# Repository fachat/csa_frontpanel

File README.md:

# CS/A frontpanel design

This repo defines a front panel with toggle switches and push buttons to
read data from and write data to CS/A memory bus.

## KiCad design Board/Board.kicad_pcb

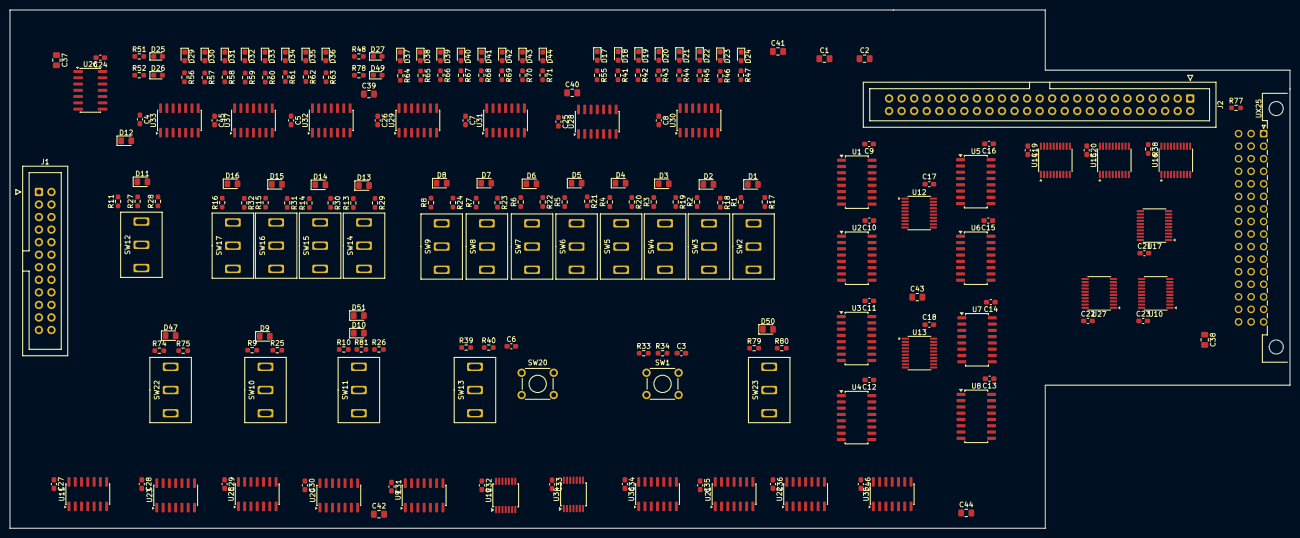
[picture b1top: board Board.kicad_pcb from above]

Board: 2 copper layers, 259.1 x 104.9 mm, 221 parts (0 on the bottom side), 267 nets, no tracks yet.

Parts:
C1, C2, C37, C38, C39, C40, C41, C42, C43, C44: 47u; C_0805_2012Metric_Pad1.18x1.45mm_HandSolder
C3, C4, C5, C6, C7, C8, C9, C10, C11, C12, C13, C14, C15, C16, C17, C18, C19, C20, C21, C22, C23, C24, C25, C26, C27, C28, C29, C30, C31, C32, C33, C34, C35, C36, C45, C46: 100n; C_0603_1608Metric_Pad1.08x0.95mm_HandSolder
D1, D2, D3, D4, D5, D6, D7, D8, D9, D10, D11, D12, D13, D14, D15, D16, D47, D50, D51: LED; LED_0805_2012Metric_Pad1.15x1.40mm_HandSolder
D17, D18, D19, D20, D21, D22, D23, D24, D25, D26, D27, D29, D30, D31, D32, D33, D34, D35, D36, D37, D38, D39, D40, D41, D42, D43, D44, D49: LED; LED_0603_1608Metric_Pad1.05x0.95mm_HandSolder
J1: Conn_02x12_Odd_Even; IDC-Header_2x12_P2.54mm_Vertical
J2: Conn_02x25_Odd_Even; IDC-Header_2x25_P2.54mm_Vertical
R1, R2, R3, R4, R5, R6, R7, R8, R9, R10, R11, R13, R14, R15, R16, R34, R38, R40, R74, R77, R79: 10k; R_0603_1608Metric_Pad0.98x0.95mm_HandSolder
R17, R18, R19, R20, R21, R22, R23, R24, R25, R26, R27, R28, R29, R30, R31, R32, R41, R42, R43, R44, R45, R46, R47, R48, R51, R52, R55, R56, R57, R58, R59, R60, R61, R62, R63, R64, R65, R66, R67, R68, R69, R70, R71, R75, R78, R80, R81: 560; R_0603_1608Metric_Pad0.98x0.95mm_HandSolder
R33, R39: 1k; R_0603_1608Metric_Pad0.98x0.95mm_HandSolder
SW1, SW20: SW_SPST; SW_TH_Tactile_Omron_B3F-107x
SW2, SW3, SW4, SW5, SW6, SW7, SW8, SW9, SW10, SW11, SW12, SW13, SW14, SW15, SW16, SW17, SW22, SW23: SW_SPDT; SW_K4625
U1, U2, U3, U4: 74LS257; SOP-16_4.4x10.4mm_P1.27mm
U5, U6, U7, U8: 74LS283; SOP-16_4.4x10.4mm_P1.27mm
U9: 74LS08; SOIC-14_3.9x8.7mm_P1.27mm
U10: 74LS573; TSSOP-20_4.4x6.5mm_P0.65mm
U11: 74LS32; SOIC-14_3.9x8.7mm_P1.27mm
U12, U13, U27: 74LS273; TSSOP-20_4.4x6.5mm_P0.65mm
U14, U15, U16, U17: 74LS245; TSSOP-20_4.4x6.5mm_P0.65mm
U19, U34: 74LS14; TSSOP-14_4.4x5mm_P0.65mm
U20: 74HCT00; SOIC-14_3.9x8.7mm_P1.27mm
U21, U22, U25, U36: 74HCT74; SOIC-14_3.9x8.7mm_P1.27mm
U23: 74HCT02; SOIC-14_3.9x8.7mm_P1.27mm
U26, U28, U29, U30, U31, U32, U33, U35, U37: 74LS06; SOIC-14_3.9x8.7mm_P1.27mm
UX25: CSASHORTBUSFA; DIN41612_C2_3x16_Male_Horizontal_THT

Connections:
A0: U5.5 (A1), U12.2 (Q0), U14.2 (A0), U31.5
A1: U5.3 (A2), U12.5 (Q1), U14.3 (A1), U31.9
A2: U5.14 (A3), U12.6 (Q2), U14.4 (A2), U31.11
A3: U5.12 (A4), U12.9 (Q3), U14.5 (A3), U31.13
A4: U6.5 (A1), U12.12 (Q4), U14.6 (A4), U32.1
A5: U6.3 (A2), U12.15 (Q5), U14.7 (A5), U32.3
A6: U6.14 (A3), U12.16 (Q6), U14.8 (A6), U32.5
A7: U6.12 (A4), U12.19 (Q7), U14.9 (A7), U32.9
A8: U7.5 (A1), U13.2 (Q0), U15.2 (A0), U32.11
A9: U7.3 (A2), U13.5 (Q1), U15.3 (A1), U32.13
A10: U7.14 (A3), U13.6 (Q2), U15.4 (A2), U33.1
A11: U7.12 (A4), U13.9 (Q3), U15.5 (A3), U33.3
A12: U8.5 (A1), U13.12 (Q4), U15.6 (A4), U33.5
A13: U8.3 (A2), U13.15 (Q5), U15.7 (A5), U33.9
A14: U8.14 (A3), U13.16 (Q6), U15.8 (A6), U33.11
A15: U8.12 (A4), U13.19 (Q7), U15.9 (A7), U33.13
A16: R13.1, SW14.2 (B), U16.2 (A0), U37.5
A17: R14.1, SW15.2 (B), U16.3 (A1), U37.9
A18: R15.1, SW16.2 (B), U16.4 (A2), U37.13
A19: R16.1, SW17.2 (B), U16.5 (A3), U37.1
ACTIVE: U9.4, U22.9 (Q), U23.6, U23.9, U35.5
B2PHI2: J2.48, UX25.c15 (2PHI2)
B8PHI2: J2.47, UX25.b16 (8PHI2)
BA0: J2.33, U14.18 (B0), UX25.c11 (A0)
BA1: J2.29, U14.17 (B1), UX25.b10 (A1)
BA2: J2.30, U14.16 (B2), UX25.c10 (A2)
BA3: J2.26, U14.15 (B3), UX25.b9 (A3)
BA4: J2.27, U14.14 (B4), UX25.c9 (A4)
BA5: J2.23, U14.13 (B5), UX25.b8 (A5)
BA6: J2.24, U14.12 (B6), UX25.c8 (A6)
BA7: J2.20, U14.11 (B7), UX25.b7 (A7)
BA8: J2.21, U15.18 (B0), UX25.c7 (A8)
BA9: J2.17, U15.17 (B1), UX25.b6 (A9)
BA10: J2.18, U15.16 (B2), UX25.c6 (A10)
BA11: J2.14, U15.15 (B3), UX25.b5 (A11)
BA12: J2.15, U15.14 (B4), UX25.c5 (A12)
BA13: J2.11, U15.13 (B5), UX25.b4 (A13)
BA14: J2.12, U15.12 (B6), UX25.c4 (A14)
BA15: J2.9, U15.11 (B7), UX25.b3 (A15)
BA16: J2.8, U16.18 (B0), UX25.c3 (A16)
BA17: J2.5, U16.17 (B1), UX25.b2 (A17)
BA18: J2.6, U16.16 (B2), UX25.c2 (A18)
BA19: J2.3, U16.15 (B3), UX25.b1 (A19)
BD0: J2.34, U10.2 (D0), U17.2 (A0), UX25.a12 (D0)
BD1: J2.31, U10.3 (D1), U17.3 (A1), UX25.a11 (D1)
BD2: J2.28, U10.4 (D2), U17.4 (A2), UX25.a10 (D2)
BD3: J2.25, U10.5 (D3), U17.5 (A3), UX25.a9 (D3)
BD4: J2.22, U10.6 (D4), U17.6 (A4), UX25.a8 (D4)
BD5: J2.19, U10.7 (D5), U17.7 (A5), UX25.a7 (D5)
BD6: J2.16, U10.8 (D6), U17.8 (A6), UX25.a6 (D6)
BD7: J2.13, U10.9 (D7), U17.9 (A7), UX25.a5 (D7)
BPHI1: J2.39, UX25.c13 (PHI1)
BPHI2: J2.42, U10.11 (Load), U19.3, UX25.c12 (PHI2)
BRDY: J2.38, U19.5, U35.4, UX25.b13 (RDY)
BR/-W: J2.35, U16.14 (B4), UX25.b12 (R/-W)
BSYNC: J2.32, UX25.b11 (SYNC)
BV33: C2.1, J2.41, UX25.b14 (VCC33)
CLK: U19.8, U19.11, U20.9, U22.3 (C), U25.13 (~R), U36.13 (~R)
CLKIN: C6.1, J1.4, R39.2, R40.2, U19.9
CLK_H: U13.11 (Cp), U23.4
CLK_L: U12.11 (Cp), U23.10
CLK_RD: U9.9, U11.1, U22.8 (~Q), U23.12, U25.11 (C), U27.11 (Cp), U36.11 (C)
D0IN: J1.6, R1.2, SW2.2 (B), U1.2 (I0a), U3.2 (I0a), U17.18 (B0), U28.11
D1IN: J1.8, R2.1, SW3.2 (B), U1.5 (I0b), U3.5 (I0b), U17.17 (B1), U28.1
D2IN: J1.10, R3.1, SW4.2 (B), U1.14 (I0c), U3.14 (I0c), U17.16 (B2), U28.3
D3IN: J1.12, R4.1, SW5.2 (B), U1.11 (I0d), U3.11 (I0d), U17.15 (B3), U28.5
D4IN: J1.14, R5.1, SW6.2 (B), U2.2 (I0a), U4.2 (I0a), U17.14 (B4), U28.9
D5IN: J1.16, R6.1, SW7.2 (B), U2.5 (I0b), U4.5 (I0b), U17.13 (B5), U28.13
D6IN: J1.18, R7.1, SW8.2 (B), U2.14 (I0c), U4.14 (I0c), U17.12 (B6), U29.11
D7IN: J1.20, R8.1, SW9.2 (B), U2.11 (I0d), U4.11 (I0d), U17.11 (B7), U29.1
DIN0: J1.5, U27.2 (Q0), U30.1
DIN1: J1.7, U27.5 (Q1), U30.3
DIN2: J1.9, U27.6 (Q2), U30.5
DIN3: J1.11, U27.9 (Q3), U30.9
DIN4: J1.13, U27.12 (Q4), U30.11
DIN5: J1.15, U27.15 (Q5), U30.13
DIN6: J1.17, U27.16 (Q6), U31.1
DIN7: J1.19, U27.19 (Q7), U31.3
GND: C1.2, C2.2, C3.2, C4.2, C5.2, C6.2, C7.2, C8.2, C9.2, C10.2, C11.2, C12.2, C13.2, C14.2, C15.2, C16.2, C17.2, C18.2, C19.2, C20.2, C21.2, C22.2, C23.2, C24.2, C25.2, C26.2, C27.2, C28.2, C29.2, C30.2, C31.2, C32.2, C33.2, C34.2, C35.2, C36.2, C37.2, C38.2, C39.2, C40.2, C41.2, C42.2, C43.2, C44.2, C45.2, C46.2, J1.23, J2.1, J2.49, R77.2, SW1.1 (A), SW2.3 (C), SW3.3 (C), SW4.3 (C), SW5.3 (C), SW6.3 (C), SW7.3 (C), SW8.3 (C), SW9.3 (C), SW10.3 (C), SW11.3 (C), SW12.3 (C), SW13.1 (A), SW14.3 (C), SW15.3 (C), SW16.3 (C), SW17.3 (C), SW20.1 (A), SW22.3 (C), SW23.3 (C), U1.8 (GND), U1.15 (OE), U2.8 (GND), U2.15 (OE), U3.8 (GND), U3.15 (OE), U4.8 (GND), U4.15 (OE), U5.2 (B2), U5.6 (B1), U5.8 (GND), U5.11 (B4), U5.15 (B3), U6.2 (B2), U6.6 (B1), U6.8 (GND), U6.11 (B4), U6.15 (B3), U7.2 (B2), U7.6 (B1), U7.8 (GND), U7.11 (B4), U7.15 (B3), U8.2 (B2), U8.6 (B1), U8.8 (GND), U8.11 (B4), U8.15 (B3), U9.7 (GND), U10.1 (OE), U10.10 (GND), U11.7 (GND), U12.10 (GND), U13.10 (GND), U14.10 (GND), U15.10 (GND), U16.10 (GND), U17.1 (A->B), U17.10 (GND), U19.7 (GND), U20.7 (GND), U21.7 (GND), U22.7 (GND), U23.7 (GND), U25.7 (GND), U26.7 (GND), U27.10 (GND), U28.7 (GND), U29.7 (GND), U30.7 (GND), U31.7 (GND), U32.7 (GND), U33.7 (GND), U34.7 (GND), U35.7 (GND), U36.14 (VCC), U37.7 (GND), UX25.a1 (GND), UX25.a16 (GND2)
INC: R9.1, SW10.2 (B), U29.5, U34.13
INCEFF: U5.7 (C0), U23.1
unnamed: D1.2 (A), R17.1
unnamed: D1.1 (K), U28.10
unnamed: D2.2 (A), R18.1
unnamed: D2.1 (K), U28.2
unnamed: D3.2 (A), R19.1
unnamed: D3.1 (K), U28.4
unnamed: D4.2 (A), R20.1
unnamed: D4.1 (K), U28.6
unnamed: D5.2 (A), R21.1
unnamed: D5.1 (K), U28.8
unnamed: D6.2 (A), R22.1
unnamed: D6.1 (K), U28.12
unnamed: D7.2 (A), R23.1
unnamed: D7.1 (K), U29.10
unnamed: D8.2 (A), R24.1
unnamed: D8.1 (K), U29.2
unnamed: D9.2 (A), R25.1
unnamed: D9.1 (K), U29.6
unnamed: D10.2 (A), R26.1
unnamed: D10.1 (K), U29.8
unnamed: D11.2 (A), R27.1
unnamed: D11.1 (K), U29.12
unnamed: D12.2 (A), R28.1
unnamed: D12.1 (K), U35.2
unnamed: D13.2 (A), R29.1
unnamed: D13.1 (K), U37.6
unnamed: D14.2 (A), R30.1
unnamed: D14.1 (K), U37.8
unnamed: D15.2 (A), R31.1
unnamed: D15.1 (K), U37.12
unnamed: D16.2 (A), R32.1
unnamed: D16.1 (K), U37.2
unnamed: D17.2 (A), R55.1
unnamed: D17.1 (K), U31.4
unnamed: D18.2 (A), R41.1
unnamed: D18.1 (K), U31.2
unnamed: D19.2 (A), R42.1
unnamed: D19.1 (K), U30.12
unnamed: D20.2 (A), R43.1
unnamed: D20.1 (K), U30.10
unnamed: D21.2 (A), R44.1
unnamed: D21.1 (K), U30.8
unnamed: D22.2 (A), R45.1
unnamed: D22.1 (K), U30.6
unnamed: D23.2 (A), R46.1
unnamed: D23.1 (K), U30.4
unnamed: D24.2 (A), R47.1
unnamed: D24.1 (K), U30.2
unnamed: D25.1 (K), R51.2
unnamed: D26.1 (K), R52.2
unnamed: D27.1 (K), R48.2
unnamed: D29.2 (A), R56.1
unnamed: D29.1 (K), U33.12
unnamed: D30.2 (A), R57.1
unnamed: D30.1 (K), U33.10
unnamed: D31.2 (A), R58.1
unnamed: D31.1 (K), U33.8
unnamed: D32.2 (A), R59.1
unnamed: D32.1 (K), U33.6
unnamed: D33.2 (A), R60.1
unnamed: D33.1 (K), U33.4
unnamed: D34.2 (A), R61.1
unnamed: D34.1 (K), U33.2
unnamed: D35.2 (A), R62.1
unnamed: D35.1 (K), U32.12
unnamed: D36.2 (A), R63.1
unnamed: D36.1 (K), U32.10
unnamed: D37.2 (A), R64.1
unnamed: D37.1 (K), U32.8
unnamed: D38.2 (A), R65.1
unnamed: D38.1 (K), U32.6
unnamed: D39.2 (A), R66.1
unnamed: D39.1 (K), U32.4
unnamed: D40.2 (A), R67.1
unnamed: D40.1 (K), U32.2
unnamed: D41.2 (A), R68.1
unnamed: D41.1 (K), U31.12
unnamed: D42.2 (A), R69.1
unnamed: D42.1 (K), U31.10
unnamed: D43.2 (A), R70.1
unnamed: D43.1 (K), U31.8
unnamed: D44.2 (A), R71.1
unnamed: D44.1 (K), U31.6
unnamed: D47.2 (A), R75.1
unnamed: D47.1 (K), U37.4
unnamed: D49.1 (K), R78.2
unnamed: D50.2 (A), R80.1
unnamed: D50.1 (K), U37.10
unnamed: D51.2 (A), R81.1
unnamed: D51.1 (K), U29.4
unnamed: R48.1, U26.12
unnamed: R51.1, U26.8
unnamed: R52.1, U26.6
unnamed: R78.1, U26.10
unnamed: R33.1, SW1.2 (B)
unnamed: R39.1, SW13.2 (B), SW20.2 (B)
unnamed: U1.3 (I1a), U5.4 (S1)
unnamed: U1.6 (I1b), U5.1 (S2)
unnamed: U1.13 (I1c), U5.13 (S3)
unnamed: U1.10 (I1d), U5.10 (S4)
unnamed: U1.4 (Za), U12.3 (D0)
unnamed: U1.7 (Zb), U12.4 (D1)
unnamed: U1.12 (Zc), U12.7 (D2)
unnamed: U1.9 (Zd), U12.8 (D3)
unnamed: U2.3 (I1a), U6.4 (S1)
unnamed: U2.6 (I1b), U6.1 (S2)
unnamed: U2.13 (I1c), U6.13 (S3)
unnamed: U2.10 (I1d), U6.10 (S4)
unnamed: U3.3 (I1a), U7.4 (S1)
unnamed: U3.6 (I1b), U7.1 (S2)
unnamed: U3.13 (I1c), U7.13 (S3)
unnamed: U3.10 (I1d), U7.10 (S4)
unnamed: U4.3 (I1a), U8.4 (S1)
unnamed: U4.6 (I1b), U8.1 (S2)
unnamed: U4.13 (I1c), U8.13 (S3)
unnamed: U4.10 (I1d), U8.10 (S4)
unnamed: U5.9 (C4), U6.7 (C0)
unnamed: U6.9 (C4), U7.7 (C0)
unnamed: U7.9 (C4), U8.7 (C0)
unnamed: U9.8, U9.13
unnamed: U10.19 (Q0), U27.3 (D0)
unnamed: U10.18 (Q1), U27.4 (D1)
unnamed: U10.17 (Q2), U27.7 (D2)
unnamed: U10.16 (Q3), U27.8 (D3)
unnamed: U10.15 (Q4), U27.13 (D4)
unnamed: U10.14 (Q5), U27.14 (D5)
unnamed: U10.13 (Q6), U27.17 (D6)
unnamed: U10.12 (Q7), U27.18 (D7)
unnamed: U9.11, U11.4
unnamed: U11.5, U23.13
unnamed: U9.2, U11.6
unnamed: U2.4 (Za), U12.13 (D4)
unnamed: U2.7 (Zb), U12.14 (D5)
unnamed: U2.12 (Zc), U12.17 (D6)
unnamed: U2.9 (Zd), U12.18 (D7)
unnamed: U3.4 (Za), U13.3 (D0)
unnamed: U3.7 (Zb), U13.4 (D1)
unnamed: U3.12 (Zc), U13.7 (D2)
unnamed: U3.9 (Zd), U13.8 (D3)
unnamed: U4.4 (Za), U13.13 (D4)
unnamed: U4.7 (Zb), U13.14 (D5)
unnamed: U4.12 (Zc), U13.17 (D6)
unnamed: U4.9 (Zd), U13.18 (D7)
unnamed: R77.1, U16.9 (A7)
unnamed: U19.6, U20.1
unnamed: U9.10, U20.3, U23.11
unnamed: U20.8, U34.9
unnamed: U20.10, U20.11
unnamed: U21.5 (Q), U21.12 (D), U26.9
unnamed: U21.6 (~Q), U23.5, U26.5
unnamed: U21.9 (Q), U22.2 (D), U26.13
unnamed: U21.8 (~Q), U23.8, U26.11
unnamed: U19.4, U19.13, U22.11 (C)
unnamed: U9.3, U22.12 (D)
unnamed: U23.3, U34.12
unnamed: U19.12, U25.3 (C)
unnamed: U9.1, U25.5 (Q)
unnamed: U29.3, U34.10
unnamed: U9.5, U34.4
unnamed: U9.6, U35.3
OPENHIGH: R38.2, U11.12, U11.13, U14.1 (A->B), U15.1 (A->B), U16.1 (A->B), U20.4, U20.5, U21.2 (D), U21.4 (~S), U21.10 (~S), U22.4 (~S), U22.10 (~S), U22.13 (~R), U25.1 (~R), U25.4 (~S), U25.10 (~S), U35.9, U35.11, U35.13, U36.1 (~R), U36.2 (D), U36.3 (C), U36.4 (~S), U36.10 (~S), U36.12 (D)
RES: U19.2, U34.1
S1+: U11.9, U23.2, U25.12 (D), U36.9 (Q)
S2+: U20.13, U25.9 (Q)
SEL: U1.1 (S), U2.1 (S), U3.1 (S), U4.1 (S), U22.5 (Q), U25.2 (D)
SINGLE: R74.1, SW22.2 (B), U20.12, U37.3
UPET: R79.1, SW23.2 (B), U20.2, U34.3, U37.11
VBUF: J2.46, UX25.b15 (VBUF)
VCC: C1.1, C4.1, C5.1, C7.1, C8.1, C9.1, C10.1, C11.1, C12.1, C13.1, C14.1, C15.1, C16.1, C17.1, C18.1, C19.1, C20.1, C21.1, C22.1, C23.1, C24.1, C25.1, C26.1, C27.1, C28.1, C29.1, C30.1, C31.1, C32.1, C33.1, C34.1, C35.1, C36.1, C37.1, C38.1, C39.1, C40.1, C41.1, C42.1, C43.1, C44.1, C45.1, C46.1, D25.2 (A), D26.2 (A), D27.2 (A), D49.2 (A), J1.1, J2.2, J2.50, R1.1, R2.2, R3.2, R4.2, R5.2, R6.2, R7.2, R8.2, R9.2, R10.1, R11.2, R13.2, R14.2, R15.2, R16.2, R17.2, R18.2, R19.2, R20.2, R21.2, R22.2, R23.2, R24.2, R25.2, R26.2, R27.2, R28.2, R29.2, R30.2, R31.2, R32.2, R34.1, R38.1, R40.1, R41.2, R42.2, R43.2, R44.2, R45.2, R46.2, R47.2, R55.2, R56.2, R57.2, R58.2, R59.2, R60.2, R61.2, R62.2, R63.2, R64.2, R65.2, R66.2, R67.2, R68.2, R69.2, R70.2, R71.2, R74.2, R75.2, R79.2, R80.2, R81.2, U1.16 (VCC), U2.16 (VCC), U3.16 (VCC), U4.16 (VCC), U5.16 (VCC), U6.16 (VCC), U7.16 (VCC), U8.16 (VCC), U9.14 (VCC), U10.20 (VCC), U11.14 (VCC), U12.20 (VCC), U13.20 (VCC), U14.20 (VCC), U15.20 (VCC), U16.20 (VCC), U17.20 (VCC), U19.14 (VCC), U20.14 (VCC), U21.14 (VCC), U22.14 (VCC), U23.14 (VCC), U25.14 (VCC), U26.14 (VCC), U27.20 (VCC), U28.14 (VCC), U29.14 (VCC), U30.14 (VCC), U31.14 (VCC), U32.14 (VCC), U33.14 (VCC), U34.14 (VCC), U35.14 (VCC), U36.7 (GND), U37.14 (VCC), UX25.c1 (VCC), UX25.c16 (VCC2)
/ACK: J1.21, U25.8 (~Q)
/ADDREN: U14.19 (CE), U15.19 (CE), U16.19 (CE)
/BBE: J2.10, U35.6, UX25.a4 (/BE)
/BIOSEL: J2.7, U16.12 (B6), UX25.a3 (/IOSEL)
/BIRQ: J2.40, UX25.a14 (/IRQ)
/BMEMSEL: J2.4, U16.13 (B5), UX25.a2 (/MEMSEL)
/BNMI: J2.37, UX25.a13 (/NMI)
/BRES: J2.43, UX25.a15 (/RES)
/CLK: U19.10, U21.3 (C), U21.11 (C)
/DOUTEN: U11.3, U17.19 (CE)
/IO: U16.8 (A6), U34.6, U35.1
/MEM: R11.1, SW12.2 (B), U16.7 (A5), U29.13, U34.5
/RES: U12.1 (~Mr), U13.1 (~Mr), U21.1 (~R), U21.13 (~R), U22.1 (~R), U27.1 (~Mr), U34.2
/RESIN: C3.1, J1.3, R33.2, R34.2, U19.1
/STOP: U9.12, U34.8
/WRITE: J1.22, R10.2, SW11.2 (B), U11.10, U29.9, U34.11
/WRITEEFF: U11.2, U11.8, U16.6 (A4)
